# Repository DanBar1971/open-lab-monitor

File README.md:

open-lab-monitor
=================

### Overview

An open hardware microcontroller device for use in research and teaching laboratory settings, and as an independent sensing node.

### PCB

- Nice reference for MAGJACK options:
http://mbed.org/cookbook/Ethernet-RJ45 
- Nice reference for uSD breakout schematic, adafruit:
https://raw.github.com/adafruit/MicroSD-breakout-board/master/usdbreakout.png
 
### Code

Code for controlling the Open Lab Monitor device, the development and goals and applications of which are documented [here](https://github.com/Pioneer-Valley-Open-Science/pioneer-valley-open-science.github.com/issues/8).

The code consists of Arduino code to be loaded on an Arduino-based sensor platform, as well as a Processing and Python interface for interacting with the platform (e.g. plotting sensor values, downloading data as a CSV file). 

#### Notes on the Arduino Code

Some non-standard Arduino libraries are required, frozen versions of which can be found [here](https://github.com/dwblair/open-lab-monitor/tree/master/arduino/libraries).  Copy (or better yet, link) the folders under "libraries" to your "libraries" folder for your Arduino sketchbook:

* ThermistorLib (cversek's library for reading thermistor values) -- latest version found [here](https://github.com/cversek/umass-physics/tree/master/teis/arduino/ThermistorLib).
                                                                  
* SerialCommand (originally Steven Cogswell's slick library for parsing commands over serial)  -- check out his surly [blog post](http://husks.wordpress.com/2011/05/23/a-minimal-arduino-library-for-processing-serial-commands/); we are using the new and improved version hosted on github [here](https://github.com/kroimon/Arduino-SerialCommand)

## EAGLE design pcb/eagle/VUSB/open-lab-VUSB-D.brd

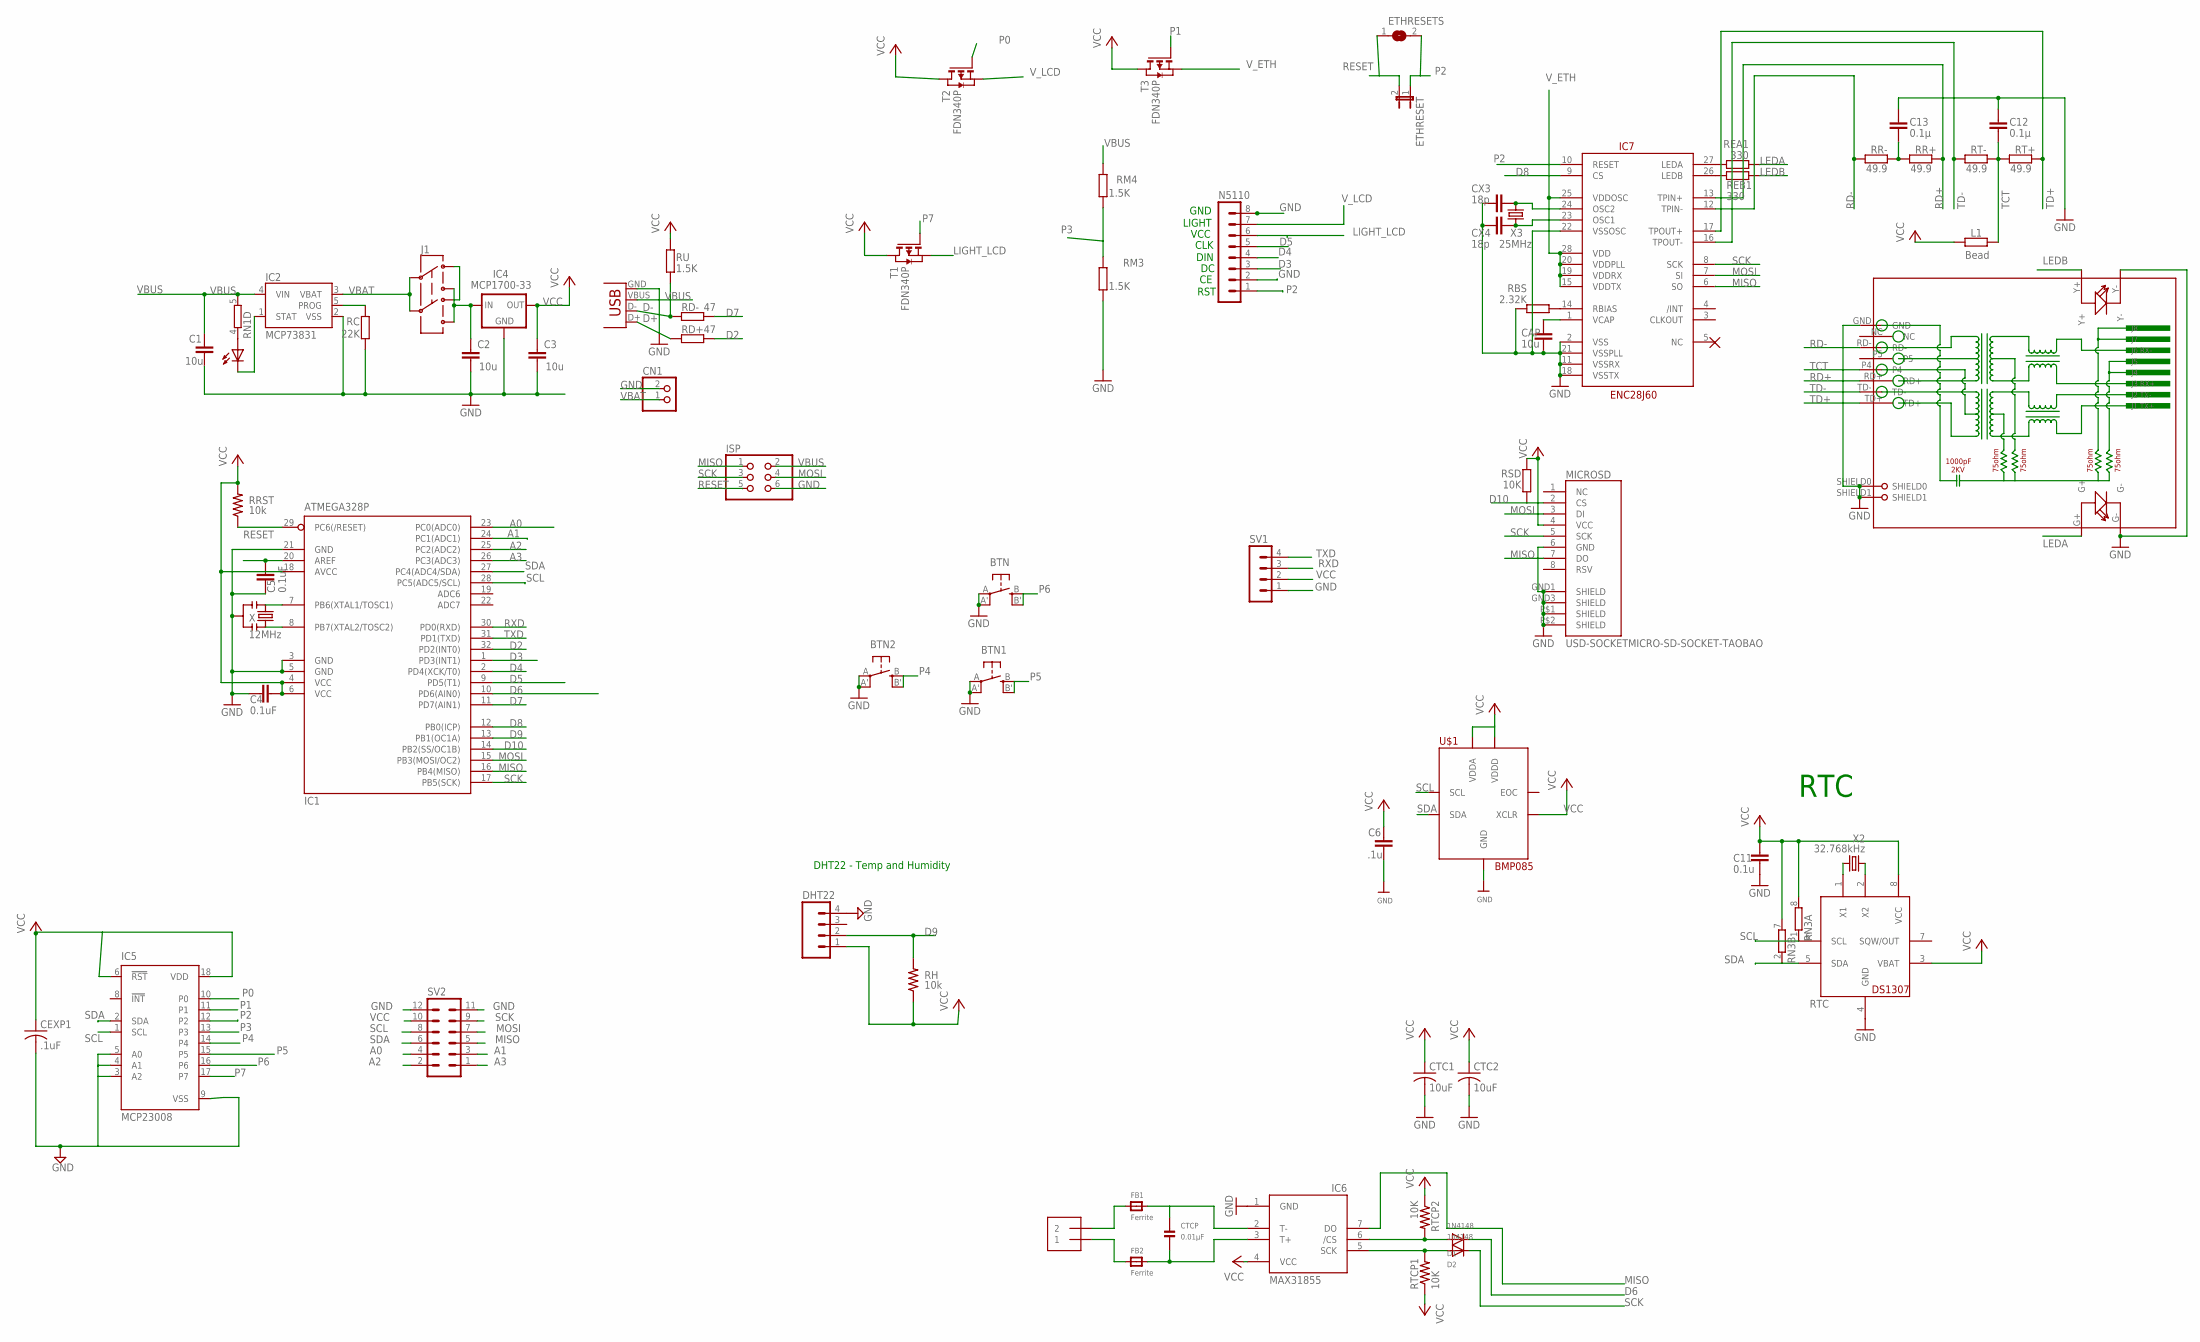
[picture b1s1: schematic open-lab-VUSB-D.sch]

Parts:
BTN, BTN1, BTN2: EVQQ2; EVQ-Q2
C1, C2, C3: 10u; C0805
C4, C5: 0.1uF; C0805
C6: .1u; C0805
C11: 0.1u; C0805
C12, C13: 0.1µ; C0805
CAP: 10u; C0805
CEXP1: .1uF; C0805K
CHG: 0805; CHIPLED_0805
CN1: JST_2PIN-SMT-RA; JST-PH-2-SMT-RA
CTC1, CTC2: 10uF; C0805K
CTCP: 0.01µF; _0805
CX3, CX4: 18p; C0805
D1: 1N4148; SOD-323F
D2: 1n4148; SOD-323F
DHT22: M04LOCK; 1X04_LOCK
ETHRESET: JP1E; JP1
ETHRESETS: SJ
FB1, FB2: Ferrite; _0805
IC1: ATMEGA328P; TQFP32-08
IC2: MCP73831; SOT23-5
IC4: MCP1700-33; SOT23
IC5: MCP23008; SO18W
IC6: MAX31855; SO08
IC7: ENC28J60; SOIC28WLONG
ISP: PINHD-2X3; 2X03
J1: AYZ0202
L1: Bead; R0805
MICROSD: USD-SOCKETMICRO-SD-SOCKET-TAOBAO; MICRO-SD-SOCKET-TAOBAO
N5110: MA08-1
RBS: 2.32K; R0805
RC: 22K; R0805
RD+: 47; R0805
RD-: 47; R0805
REA1: 330; R0805
REB1: 330; R0805
RH: 10k; R0805@1
RJ45: HR911105A
RM3, RM4: 1.5K; R0805
RN1, RN3: 4R-NEXB38V; EXB38V
RR+: 49.9; R0805
RR-: 49.9; R0805
RRST: 10k; R0805@1
RSD: 10K; R0805
RT+: 49.9; R0805
RT-: 49.9; R0805
RTC: DS1307; SO08
RTCP1, RTCP2: 10K; R0805
RU: 1.5K; R0805
SV1: MA04-1
SV2: MA06-2
T1, T2, T3: FDN340P; SOT-23
TCPL: 1X2-3.5MM
U$1: BMP085
X: 12MHz; RESONATOR-SMD
X1: USBSMD; USB-MINIB
X2: 32.768kHz; TC26H
X3: 25MHz; HC49U-V

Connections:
A0: IC1.23 (PC0(ADC0)), SV2.4
A1: IC1.24 (PC1(ADC1)), SV2.3
A2: IC1.25 (PC2(ADC2)), SV2.2
A3: IC1.26 (PC3(ADC3)), SV2.1
AREF: C5.2, IC1.20 (AREF)
CS: D1.A, IC6.6 (/CS), RTCP2.2
D2: IC1.32 (PD2(INT0)), RD+.2
D3: IC1.1 (PD3(INT1)), N5110.3
D4: IC1.2 (PD4(XCK/T0)), N5110.4
D5: IC1.9 (PD5(T1)), N5110.5
D6: D1.C, IC1.10 (PD6(AIN0))
D7: IC1.11 (PD7(AIN1)), RD-.2
D8: IC1.12 (PB0(ICP)), IC7.9 (CS)
D9: DHT22.2, IC1.13 (PB1(OC1A)), RH.2
D10: IC1.14 (PB2(SS/OC1B)), MICROSD.2 (CS), RSD.1
D+: RD+.1, X1.D+
D-: RD-.1, RU.1, X1.D-
GND: BTN.A, BTN.A' (P1), BTN1.A, BTN1.A' (P1), BTN2.A, BTN2.A' (P1), C1.2, C2.2, C3.2, C4.1, C5.1, C6.2, C11.2, C12.1, C13.1, CAP.2, CEXP1.2, CN1.2 (1), CTC1.2, CTC2.2, CX3.2, CX4.2, DHT22.4, IC1.3 (GND), IC1.5 (GND), IC1.21 (GND), IC2.2 (VSS), IC4.1 (GND), IC5.3 (A2), IC5.4 (A1), IC5.5 (A0), IC5.9 (VSS), IC6.1 (GND), IC7.2 (VSS), IC7.11 (VSSRX), IC7.18 (VSSTX), IC7.21 (VSSPLL), IC7.22 (VSSOSC), ISP.6, MICROSD.6 (GND), MICROSD.GND1 (SHIELD), MICROSD.GND3 (SHIELD), MICROSD.P$1 (SHIELD), MICROSD.P$2 (SHIELD), N5110.2, N5110.8, RBS.1, RC.1, RJ45.G-, RJ45.GND, RJ45.SHIELD0, RJ45.SHIELD1, RJ45.Y-, RM3.1, RTC.4 (GND), SV1.1, SV2.11, SV2.12, U$1.P$1 (GND), X.2, X1.GND
LEDA: REA1.2, RJ45.G+
LEDB: REB1.2, RJ45.Y+
LIGHT_LCD: N5110.6, T1.2 (S)
MISO: IC1.16 (PB4(MISO)), IC6.7 (DO), IC7.6 (SO), ISP.1, MICROSD.7 (DO), SV2.5
MOSI: IC1.15 (PB3(MOSI/OC2)), IC7.7 (SI), ISP.4, MICROSD.3 (DI), SV2.7
unnamed: J1.3 (1), J1.6 (4)
unnamed: IC1.7 (PB6(XTAL1/TOSC1)), X.1
unnamed: IC1.8 (PB7(XTAL2/TOSC2)), X.3
unnamed: CHG.C, IC2.1 (STAT)
unnamed: IC2.5 (PROG), RC.2
unnamed: FB1.1, TCPL.2
unnamed: CTCP.1, FB1.2, IC6.2 (T-)
unnamed: CHG.A, RN1.4 (1)
unnamed: FB2.1, TCPL.1
unnamed: CTCP.2, FB2.2, IC6.3 (T+)
unnamed: RTC.1 (X1), X2.2
unnamed: RTC.2 (X2), X2.1
unnamed: IC7.27 (LEDA), REA1.1
unnamed: IC7.26 (LEDB), REB1.1
unnamed: CAP.1, IC7.1 (VCAP)
unnamed: CX3.1, IC7.24 (OSC2), X3.2
unnamed: CX4.1, IC7.23 (OSC1), X3.1
unnamed: C13.2, RR+.2, RR-.1
unnamed: IC7.14 (RBIAS), RBS.2
P0: IC5.10 (P0), T2.3 (G)
P1: IC5.11 (P1), T3.3 (G)
P2: ETHRESET.1, ETHRESETS.2, IC5.12 (P2), IC7.10 (RESET), N5110.1
P3: IC5.13 (P3), RM3.2, RM4.1
P4: BTN2.B (S), BTN2.B' (S1), IC5.14 (P4)
P5: BTN1.B (S), BTN1.B' (S1), IC5.15 (P5)
P6: BTN.B (S), BTN.B' (S1), IC5.16 (P6)
P7: IC5.17 (P7), T1.3 (G)
RD+: IC7.13 (TPIN+), RJ45.RD+, RR+.1
RD-: IC7.12 (TPIN-), RJ45.RD-, RR-.2
RESET: ETHRESET.2, ETHRESETS.1, IC1.29 (PC6(/RESET)), ISP.5, RRST.1
RXD: IC1.30 (PD0(RXD)), SV1.3
SCK: D2.C, IC1.17 (PB5(SCK)), IC7.8 (SCK), ISP.3, MICROSD.5 (SCK), SV2.9
SCK1: D2.A, IC6.5 (SCK), RTCP1.2
SCL: IC1.28 (PC5(ADC5/SCL)), IC5.1 (SCL), RN3.1, RTC.6 (SCL), SV2.8, U$1.P$6 (SCL)
SDA: IC1.27 (PC4(ADC4/SDA)), IC5.2 (SDA), RN3.2 (1), RTC.5 (SDA), SV2.6, U$1.P$7 (SDA)
TCT: C12.2, L1.1, RJ45.P4, RT+.2, RT-.1
TD+: IC7.17 (TPOUT+), RJ45.TD+, RT+.1
TD-: IC7.16 (TPOUT-), RJ45.TD-, RT-.2
TXD: IC1.31 (PD1(TXD)), SV1.4
VBAT: CN1.1 (2), IC2.3 (VBAT), J1.2, J1.5
VBUS: C1.1, IC2.4 (VIN), ISP.2, RM4.2, RN1.5 (2), X1.VBUS
VCC: C3.1, C4.2, C6.1, C11.1, CEXP1.1, CTC1.1, CTC2.1, DHT22.1, IC1.4 (VCC), IC1.6 (VCC), IC1.18 (AVCC), IC4.2 (OUT), IC5.6 (!RST), IC5.18 (VDD), IC6.4 (VCC), L1.2, MICROSD.4 (VCC), RH.1, RN3.7 (2), RN3.8 (2), RRST.2, RSD.2, RTC.3 (VBAT), RTC.8 (VCC), RTCP1.1, RTCP2.1, RU.2, SV1.2, SV2.10, T1.1 (D), T2.1 (D), T3.1 (D), U$1.P$3 (VDDA), U$1.P$4 (VDDD), U$1.P$8 (XCLR)
VDD: C2.1, IC4.3 (IN), J1.1 (3), J1.4 (6)
V_ETH: IC7.15 (VDDTX), IC7.19 (VDDRX), IC7.20 (VDDPLL), IC7.25 (VDDOSC), IC7.28 (VDD), T3.2 (S)
V_LCD: N5110.7, T2.2 (S)

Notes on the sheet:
RST
DIN
CLK
VCC
LIGHT
GND
RTC
DHT22 - Temp and Humidity

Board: 2 copper layers, 72 parts (4 on the bottom side), 68 nets, no tracks yet.

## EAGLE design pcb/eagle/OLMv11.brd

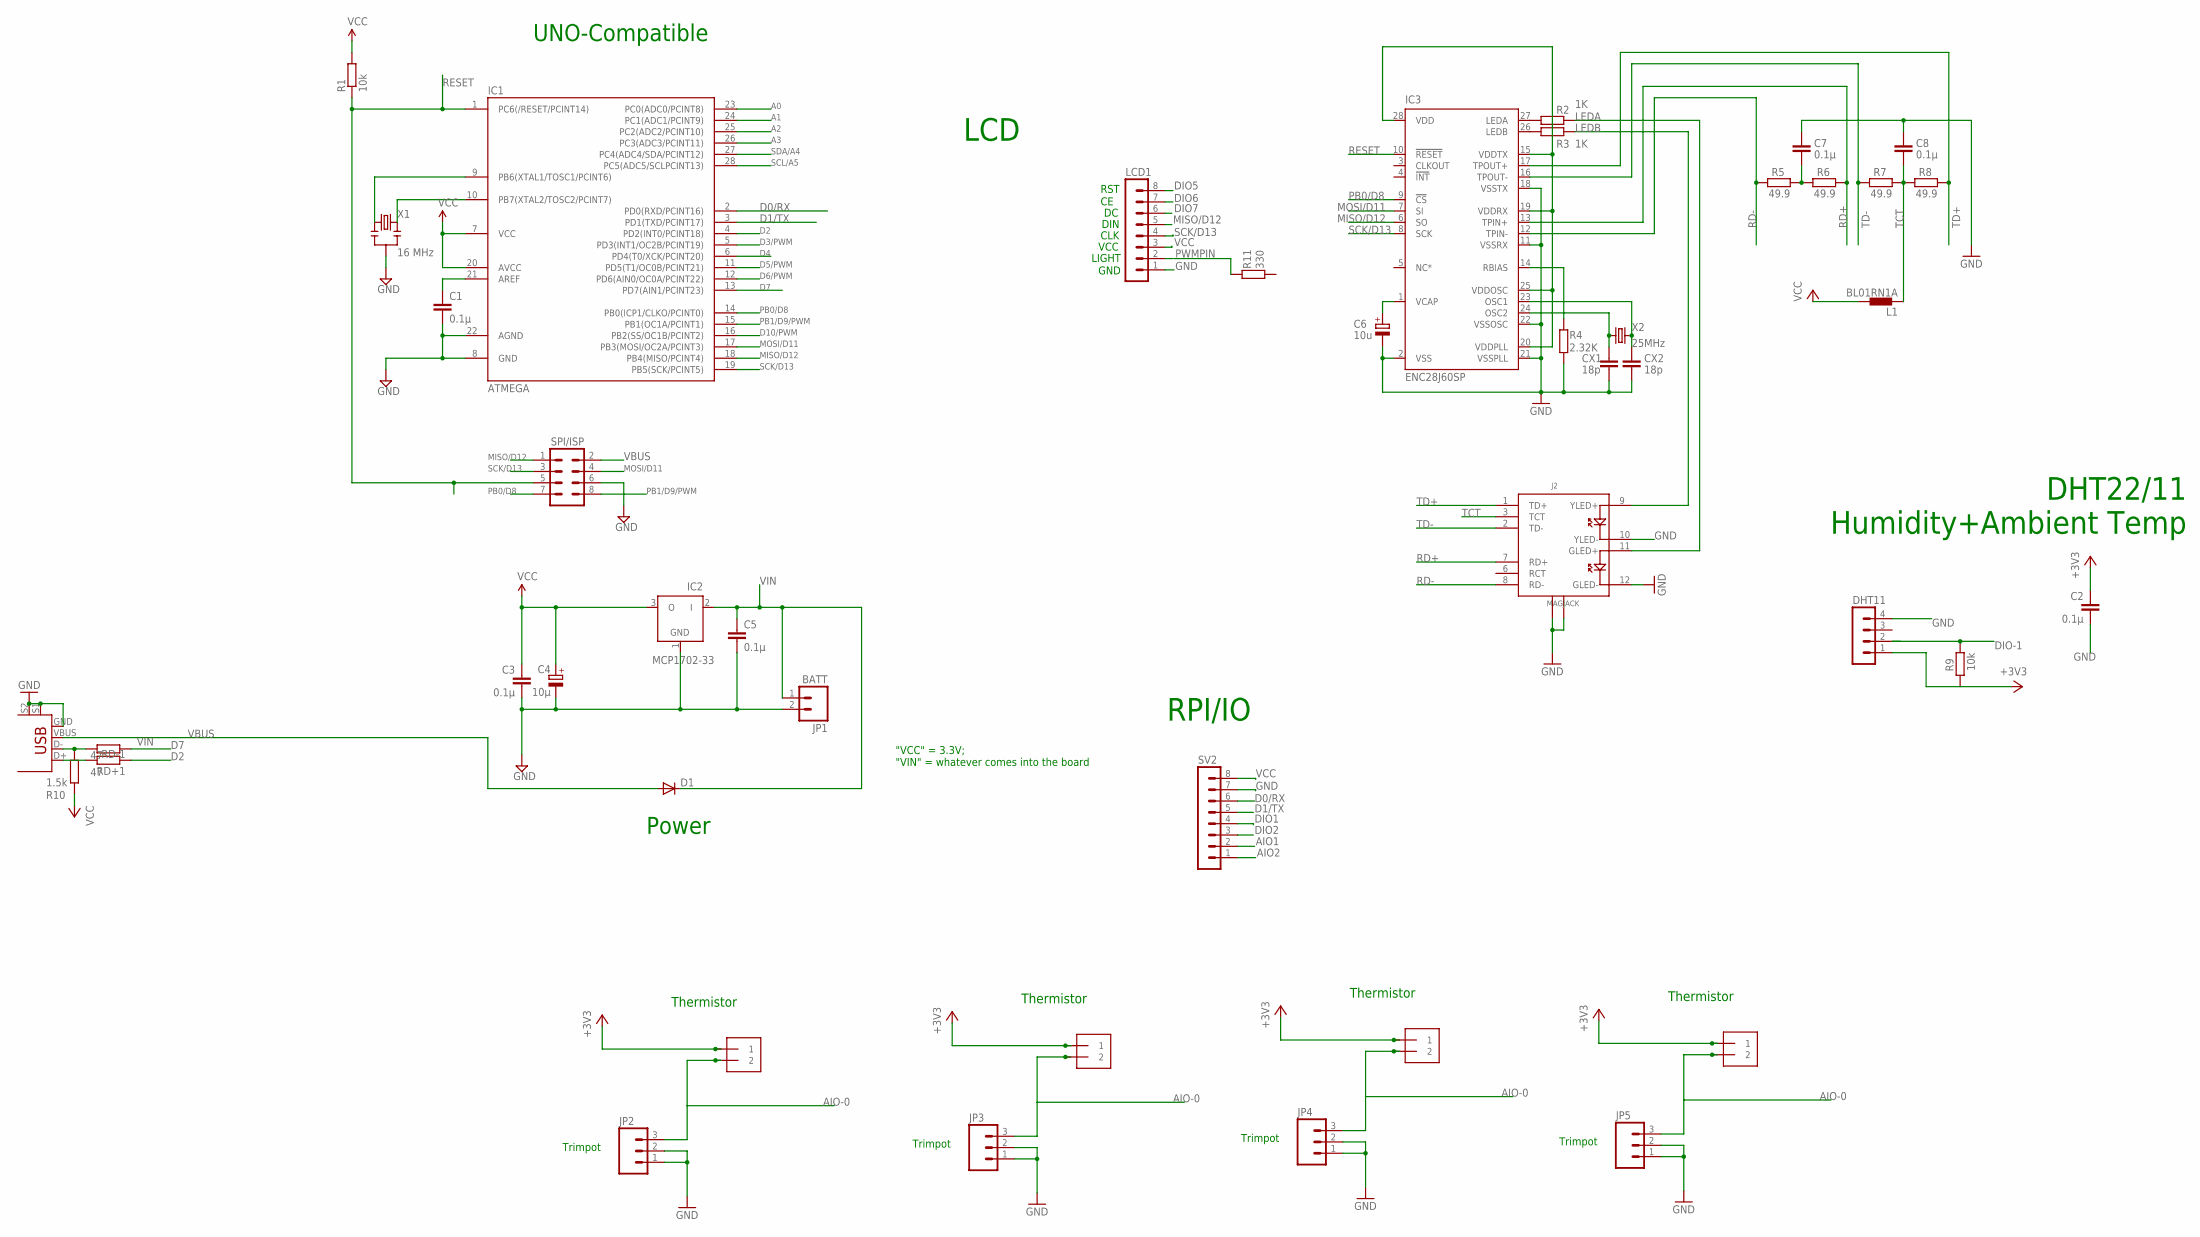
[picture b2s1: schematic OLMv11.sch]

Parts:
C1, C2, C3, C5, C7, C8: 0.1µ; C025-024X044
C4: 10µ; E1,8-4
C6: 10u; E1,8-4
CX1, CX2: 18p; C025-024X044
D1: DIODE-D-5; D-5
DHT11: MA04-1
IC1: ATMEGA; DIL28-3
IC2: MCP1702-33; TO92
IC3: ENC28J60SP; DIL28-3
J1, J3, J4, J5: 1X2-3.5MM
J2: MAGJACK
JP1: BATT; 1X02_LOCK_LONGPADS
JP2, JP3, JP4, JP5: M03PTH; 1X03
L1: BL01RN1A
LCD1: MA08-1
R1, R9: 10k; 0204/7
R2, R3: 1K; 0204/7
R4: 2.32K; 0204/7
R5, R6, R7, R8: 49.9; 0204/7
R10: 1.5k; 0204/7
R11: 330; 0204/7
RD+1: 47; 0204/7
RD-1: 47; 0204/7
SV1: SPI/ISP; MA04-2
SV2: MA08-1
USB: USB+SHIELD; USB-B-PTH
X1: 16 MHz; RESONATOR-PTH
X2: 25MHz; HC49US

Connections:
+3V3: C2.1, DHT11.1, J1.1, J3.1, J4.1, J5.1, R9.1
A0: IC1.23 (PC0(ADC0/PCINT8))
A1: IC1.24 (PC1(ADC1/PCINT9))
A2: IC1.25 (PC2(ADC2/PCINT10))
A3: IC1.26 (PC3(ADC3/PCINT11))
AIO1: SV2.2
AIO2: SV2.1
AIO-0: J1.2, J3.2, J4.2, J5.2, JP2.3, JP3.3, JP4.3, JP5.3
D0/RX: IC1.2 (PD0(RXD/PCINT16)), SV2.6
D1/TX: IC1.3 (PD1(TXD/PCINT17)), SV2.5
D2: IC1.4 (PD2(INT0/PCINT18)), RD+1.1
D3/PWM: IC1.5 (PD3(INT1/OC2B/PCINT19))
D4: IC1.6 (PD4(T0/XCK/PCINT20))
D5/PWM: IC1.11 (PD5(T1/OC0B/PCINT21))
D6/PWM: IC1.12 (PD6(AIN0/OC0A/PCINT22))
D7: IC1.13 (PD7(AIN1/PCINT23)), RD-1.1
D10/PWM: IC1.16 (PB2(SS/OC1B/PCINT2))
DIO1: SV2.4
DIO2: SV2.3
DIO5: LCD1.8
DIO6: LCD1.7
DIO7: LCD1.6
DIO-1: DHT11.2, R9.2
GND: C1.2, C2.2, C3.2, C4.-, C5.2, C6.-, C7.1, C8.1, CX1.2, CX2.2, DHT11.4, IC1.8 (GND), IC1.22 (AGND), IC2.1 (GND), IC3.2 (VSS), IC3.11 (VSSRX), IC3.18 (VSSTX), IC3.21 (VSSPLL), IC3.22 (VSSOSC), J2.10 (YLED-), J2.12 (GLED-), J2.M1 (GND1), J2.M2 (GND2), JP1.2, JP2.1, JP2.2, JP3.1, JP3.2, JP4.1, JP4.2, JP5.1, JP5.2, LCD1.1, R4.2, SV1.6, SV2.7, USB.GND, USB.S1, USB.S2, X1.2
LEDA: J2.11 (GLED+), R2.2
LEDB: J2.9 (YLED+), R3.2
MISO/D12: IC1.18 (PB4(MISO/PCINT4)), IC3.6 (SO), LCD1.5, SV1.1
MOSI/D11: IC1.17 (PB3(MOSI/OC2A/PCINT3)), IC3.7 (SI), SV1.4
unnamed: IC1.9 (PB6(XTAL1/TOSC1/PCINT6)), X1.1
unnamed: C1.1, IC1.21 (AREF)
unnamed: IC1.10 (PB7(XTAL2/TOSC2/PCINT7)), X1.3
unnamed: IC3.27 (LEDA), R2.1
unnamed: RD+1.2, USB.D+
unnamed: IC3.26 (LEDB), R3.1
unnamed: R10.1, RD-1.2, USB.D-
unnamed: C6.+, IC3.1 (VCAP)
unnamed: IC3.14 (RBIAS), R4.1
unnamed: CX1.1, IC3.24 (OSC2), X2.1
unnamed: CX2.1, IC3.23 (OSC1), X2.2
unnamed: C7.2, R5.2, R6.1
PB0/D8: IC1.14 (PB0(ICP1/CLKO/PCINT0)), IC3.9 (!CS), SV1.7
PB1/D9/PWM: IC1.15 (PB1(OC1A/PCINT1)), SV1.8
PWMPIN: LCD1.2
RD+: IC3.13 (TPIN+), J2.7 (RD+), R6.2
RD-: IC3.12 (TPIN-), J2.8 (RD-), R5.1
RESET: IC1.1 (PC6(/RESET/PCINT14)), IC3.10 (!RESET), R1.1, SV1.5
SCK/D13: IC1.19 (PB5(SCK/PCINT5)), IC3.8 (SCK), LCD1.4, SV1.3
SCL/A5: IC1.28 (PC5(ADC5/SCLPCINT13))
SDA/A4: IC1.27 (PC4(ADC4/SDA/PCINT12))
TCT: C8.2, J2.3 (TCT), L1.1, R7.2, R8.1
TD+: IC3.17 (TPOUT+), J2.1 (TD+), R8.2
TD-: IC3.16 (TPOUT-), J2.2 (TD-), R7.1
VBUS: D1.A, SV1.2
VCC: C3.1, C4.+, IC1.7 (VCC), IC1.20 (AVCC), IC2.3 (O), IC3.15 (VDDTX), IC3.19 (VDDRX), IC3.20 (VDDPLL), IC3.25 (VDDOSC), IC3.28 (VDD), L1.2, LCD1.3, R1.2, R10.2, SV2.8
VIN: C5.1, D1.C, IC2.2 (I), JP1.1, USB.VBUS

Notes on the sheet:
UNO-Compatible
Power
"VCC" = 3.3V; "VIN" = whatever comes into the board
Thermistor
DHT22/11 Humidity+Ambient Temp
Trimpot
LCD
RPI/IO
RST
DIN
CLK
VCC
LIGHT
GND

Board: 2 copper layers, 45 parts (0 on the bottom side), 36 nets, no tracks yet.

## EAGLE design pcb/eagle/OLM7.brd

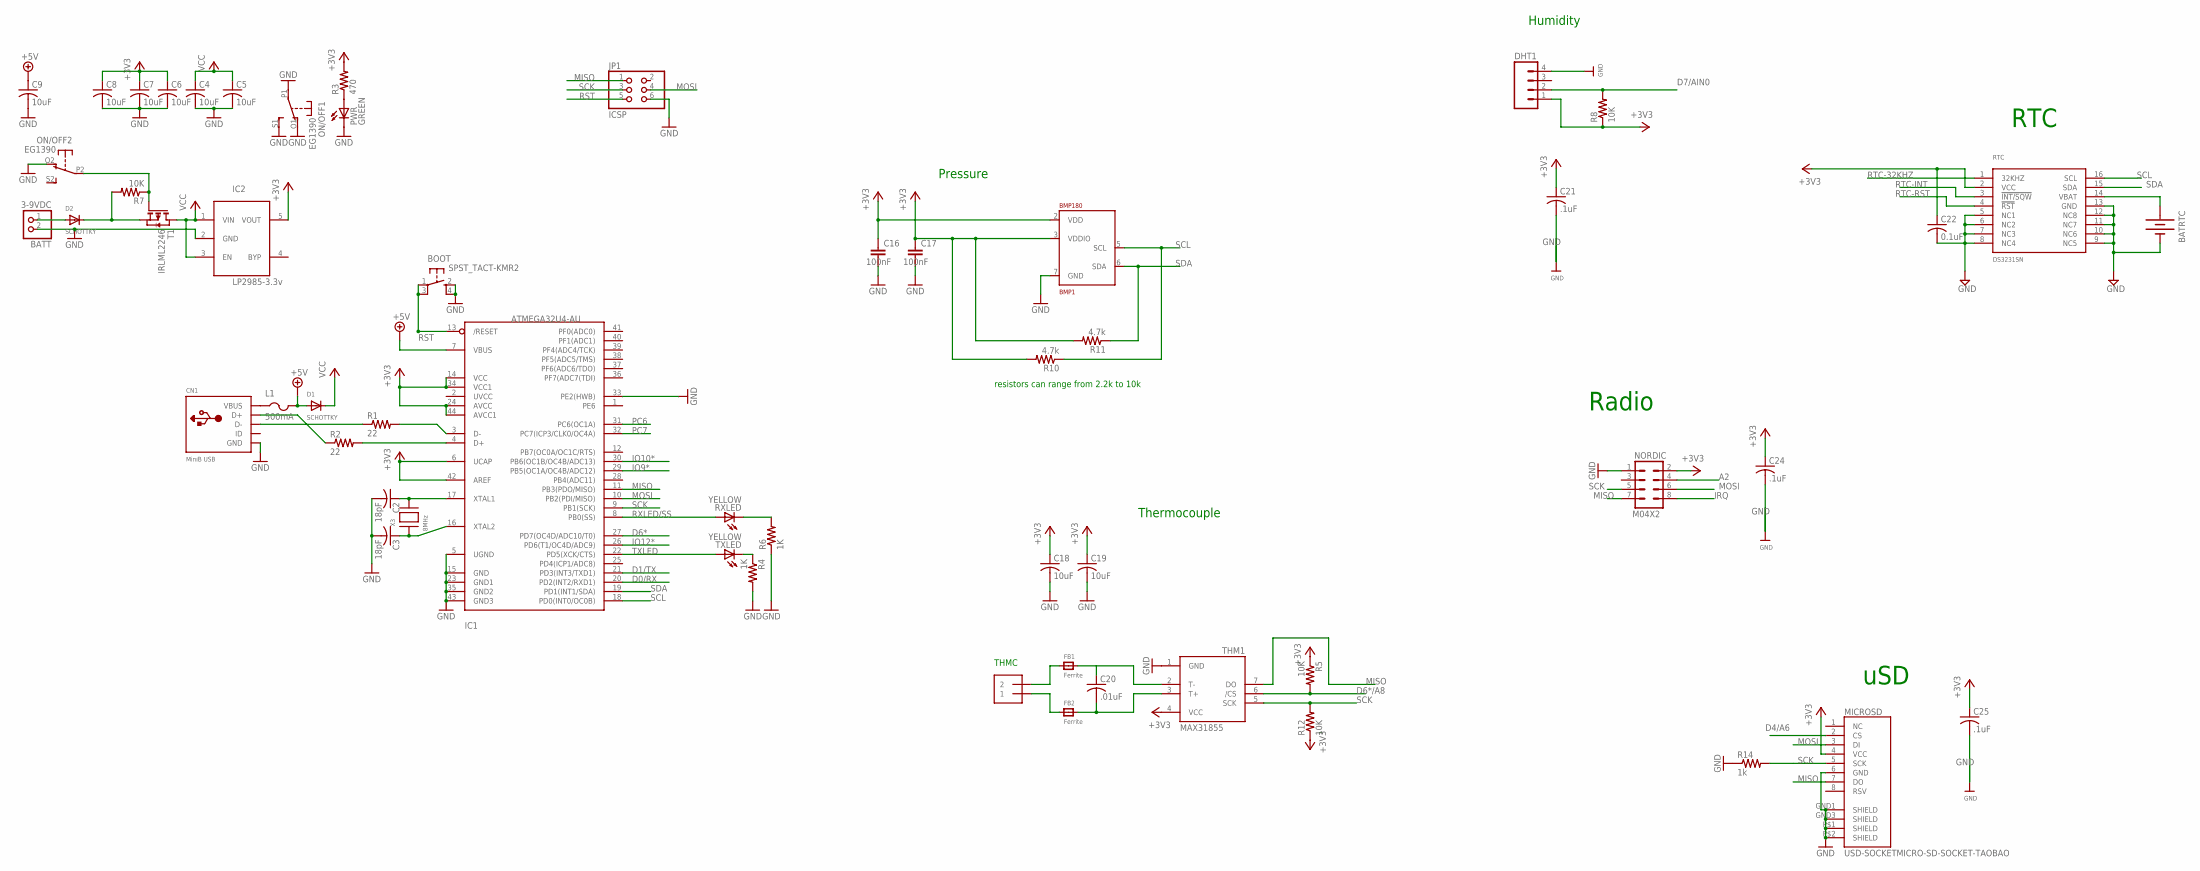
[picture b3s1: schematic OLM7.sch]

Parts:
BATRTC: BATTERYBATTERY_12MM_SMT; BATTCON_12MM_SMT
BATT: 3-9VDC; JST-PH-2-SMT-RA
BMP1: BMP180; LGA7
BOOT: SPST_TACT-KMR2; KMR2
C2, C3: 18pF; C0805K
C4, C5, C6, C7, C8, C9: 10uF; C0805K
C16, C17: 100nF; C0805
C18, C19: 10uF; C0805
C20: .01uF; C0805
C21, C24, C25: .1uF; C0805
C22: 0.1uF; C0805
CN1: MiniB USB; USB-MINIB_LARGER
D1, D2: SCHOTTKY; SOD-123
DHT1: M04LOCK; 1X04_LOCK
FB1, FB2: Ferrite; _0805
IC1: ATMEGA32U4-AU; TQFP44
IC2: LP2985-3.3v; SOT23-5L
JP1: ICSP; 2X03
L1: 500mA; R1206
MICROSD: USD-SOCKETMICRO-SD-SOCKET-TAOBAO; MICRO-SD-SOCKET-TAOBAO
NORDIC: M04X2; 2X4
ON/OFF: EG1390
PWR: GREEN; CHIPLED_0805
R1, R2: 22; R0805
R3: 470; R0805
R4, R6: 1K; R0805
R5, R7, R8, R12: 10K; R0805
R10, R11: 4.7k; R0805
R14: 1k; R0805
RTC: DS3231SN; SO16W
RXLED: YELLOW; CHIPLED_0805
T1: IRLML2246; SOT-23
THM1: MAX31855; SO08
THMC: 1X2-3.5MM
TXLED: YELLOW; CHIPLED_0805
X3: 8MHz; NX5032

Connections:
+3V3: BMP1.2 (VDD), BMP1.3 (VDDIO), C6.1, C7.1, C8.1, C16.1, C17.1, C18.1, C19.1, C21.1, C22.1, C24.1, C25.1, DHT1.1, IC1.6 (UCAP), IC1.14 (VCC), IC1.24 (AVCC), IC1.34 (VCC1), IC1.42 (AREF), IC1.44 (AVCC1), IC2.5 (VOUT), MICROSD.4 (VCC), NORDIC.2, R3.2, R5.1, R8.1, R10.2, R11.2, R12.1, RTC.2 (VCC), THM1.4 (VCC)
+5V: C9.1, D1.A, IC1.7 (VBUS), L1.2
A2: NORDIC.4
D0/RX: IC1.20 (PD2(INT2/RXD1))
D1/TX: IC1.21 (PD3(INT3/TXD1))
D4/A6: MICROSD.2 (CS)
D6*: IC1.27 (PD7(OC4D/ADC10/T0))
D6*/A8: R5.2, THM1.6 (/CS)
D7/AIN0: DHT1.2, R8.2
GND: BATRTC.P$1 (-), BATT.2 (1), BMP1.7 (GND), BOOT.2 (S), BOOT.4 (S1), C2.2, C3.2, C4.2, C5.2, C6.2, C7.2, C8.2, C9.2, C16.2, C17.2, C18.2, C19.2, C21.2, C22.2, C24.2, C25.2, CN1.GND, DHT1.4, IC1.5 (UGND), IC1.15 (GND), IC1.23 (GND1), IC1.33 (PE2(HWB)), IC1.35 (GND2), IC1.43 (GND3), IC2.2 (GND), JP1.6, MICROSD.6 (GND), MICROSD.GND1 (SHIELD), MICROSD.GND3 (SHIELD), MICROSD.P$1 (SHIELD), MICROSD.P$2 (SHIELD), NORDIC.1, ON/OFF.O1 (O), ON/OFF.O2 (O), ON/OFF.P1, ON/OFF.S1 (S), PWR.C, R4.2, R6.1, R14.1, RTC.5 (NC1), RTC.6 (NC2), RTC.7 (NC3), RTC.8 (NC4), RTC.9 (NC5), RTC.10 (NC6), RTC.11 (NC7), RTC.12 (NC8), RTC.13 (GND), THM1.1 (GND)
IO9*: IC1.29 (PB5(OC1A/OC4B/ADC12))
IO10*: IC1.30 (PB6(OC1B/OC4B/ADC13))
IO12*: IC1.26 (PD6(T1/OC4D/ADC9))
IRQ: NORDIC.8
MISO: IC1.11 (PB3(PDO/MISO)), JP1.1, MICROSD.7 (DO), NORDIC.7, THM1.7 (DO)
MOSI: IC1.10 (PB2(PDI/MISO)), JP1.4, MICROSD.3 (DI), NORDIC.6
unnamed: PWR.A, R3.1
unnamed: CN1.D+, R2.1
unnamed: IC1.3 (D-), R1.2
unnamed: IC1.4 (D+), R2.2
unnamed: CN1.D-, R1.1
unnamed: D2.C, R7.2, T1.2 (S)
unnamed: BATT.1 (2), D2.A
unnamed: C2.1, IC1.17 (XTAL1), X3.P$2
unnamed: C3.1, IC1.16 (XTAL2), X3.P$1
unnamed: R4.1, TXLED.C
unnamed: R6.2, RXLED.C
unnamed: ON/OFF.P2, R7.1, T1.3 (G)
unnamed: BATRTC.P$2 (+), RTC.14 (VBAT)
unnamed: FB1.1, THMC.2
unnamed: C20.1, FB1.2, THM1.2 (T-)
unnamed: FB2.1, THMC.1
unnamed: C20.2, FB2.2, THM1.3 (T+)
PC6: IC1.31 (PC6(OC1A))
PC7: IC1.32 (PC7(ICP3/CLK0/OC4A))
RST: BOOT.1, BOOT.3 (P1), IC1.13 (/RESET), JP1.5
RTC-32KHZ: RTC.1 (32KHZ)
RTC-INT: RTC.3 (!INT/SQW)
RTC-RST: RTC.4 (!RST)
RXLED/SS: IC1.8 (PB0(SS)), RXLED.A
SCK: IC1.9 (PB1(SCK)), JP1.3, MICROSD.5 (SCK), NORDIC.5, R12.2, THM1.5 (SCK)
SCK1: R14.2
SCL: BMP1.5 (SCL), IC1.18 (PD0(INT0/OC0B)), R10.1, RTC.16 (SCL)
SDA: BMP1.6 (SDA), IC1.19 (PD1(INT1/SDA)), R11.1, RTC.15 (SDA)
TXLED: IC1.22 (PD5(XCK/CTS)), TXLED.A
VBUS: CN1.VBUS, L1.1
VCC: C4.1, C5.1, D1.C, IC2.1 (VIN), IC2.3 (EN), T1.1 (D)

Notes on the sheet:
Pressure
resistors can range from 2.2k to 10k
Thermocouple
THMC
Humidity
Radio
RTC
uSD

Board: 2 copper layers, 54 parts (0 on the bottom side), 32 nets, no tracks yet.

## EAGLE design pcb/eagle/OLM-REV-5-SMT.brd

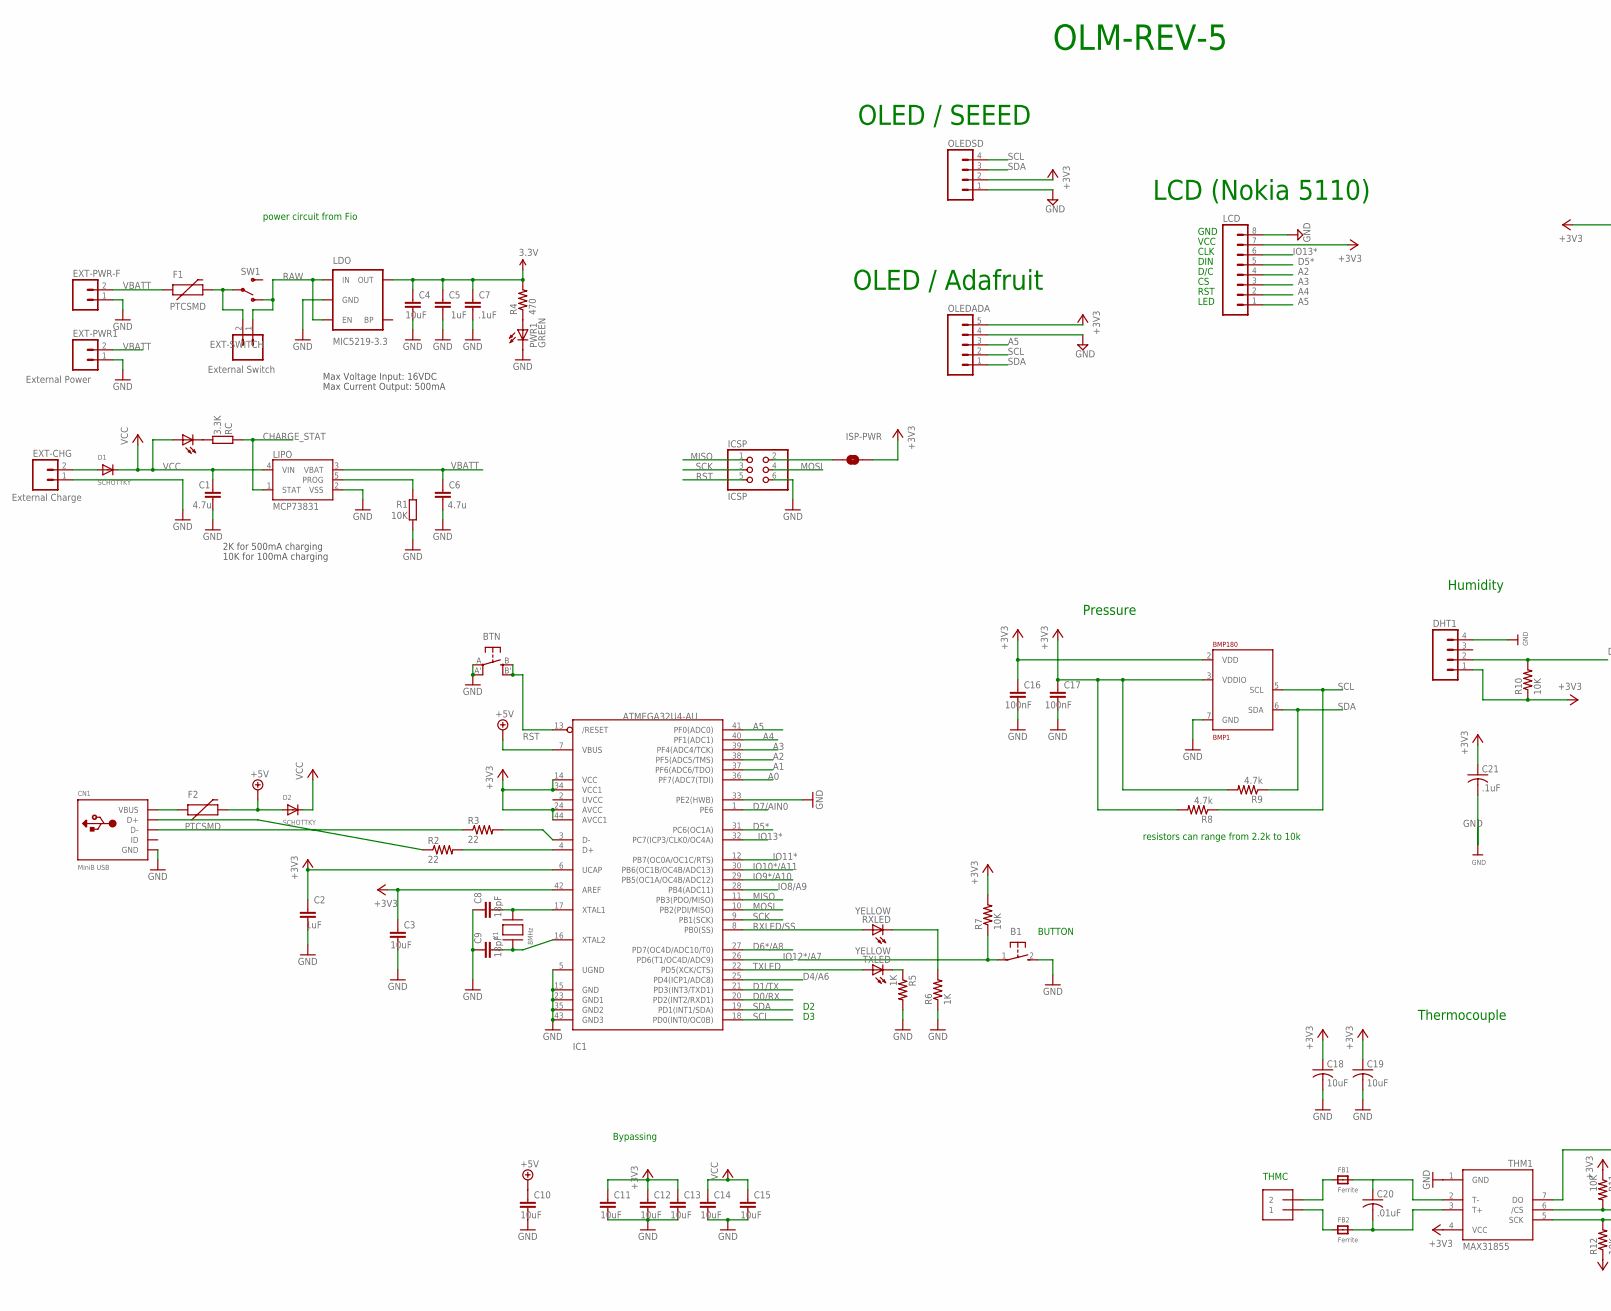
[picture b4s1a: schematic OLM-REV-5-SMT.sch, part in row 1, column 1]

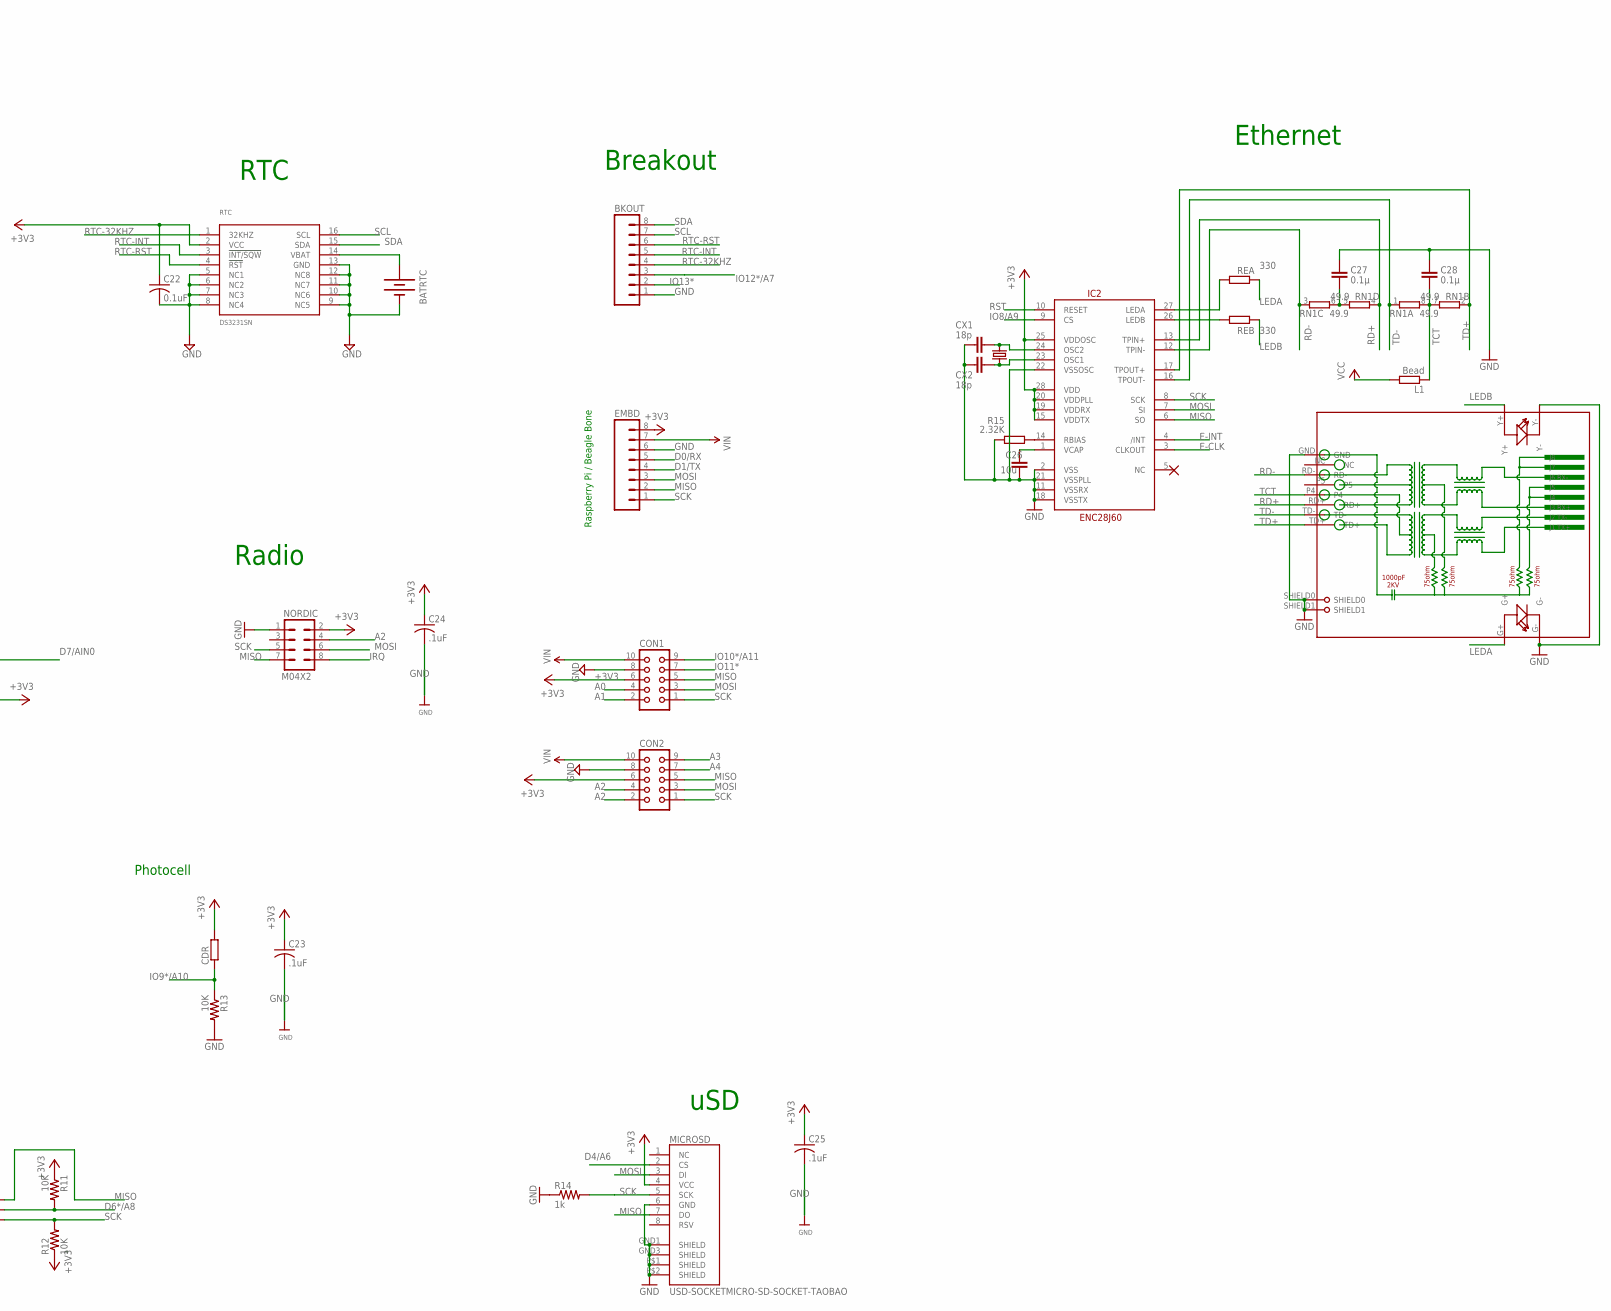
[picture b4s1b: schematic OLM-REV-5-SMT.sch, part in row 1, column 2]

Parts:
B1: 31-XX; B3F-31XX
BATRTC: BATTERYBATTERY_12MM_SMT; BATTCON_12MM_SMT
BKOUT: M08LOCK; 1X08_LOCK
BMP1: BMP180; LGA7
BTN: EVQQ2; EVQ-Q2
C1, C6: 4.7u; C0805
C2, C5: 1uF; C0805
C3, C4, C10, C11, C12, C13, C14, C15, C18, C19: 10uF; C0805
C7, C21, C23, C24, C25: .1uF; C0805
C8, C9: 18pF; C0805
C16, C17: 100nF; C0805
C20: .01uF; C0805
C22: 0.1uF; C0805
C26: 10u; C0805
C27, C28: 0.1µ; C0805
CDR: R-EU_0204/7; 0204/7
CHG1: 0805; CHIPLED_0805
CN1: MiniB USB; USB-MINIB_LARGER
CON1, CON2: CON10L
CX1, CX2: 18p; C0805
D1, D2: SCHOTTKY; SOD-123
DHT1: M04LOCK; 1X04_LOCK
EMBD: M08LOCK; 1X08_LOCK
EXT-CHG: External Charge; 1X02
EXT-PWR1: External Power; 1X02
EXT-PWR-F: M02-JST-2MM-SMT; JST-2-SMD
EXT-SWITCH: External Switch; 1X02
EXTL: 25MHz; CRYSTAL-SMD-10.5X4.8-2PIN
F1, F2: PTCSMD; PTC-1206
FB1, FB2: Ferrite; _0805
IC1: ATMEGA32U4-AU; TQFP44
IC2: ENC28J60; SOIC28WLONG
ICSP: ICSP; 2X03
ISP-PWR: SOLDERJUMPERTRACE; SJ_2S-TRACE
L1: Bead; R0805
LCD: M08LOCK; 1X08_LOCK
LDO: MIC5219-3.3; SOT23-5
LIPO: MCP73831; SOT23-5
MICROSD: USD-SOCKETMICRO-SD-SOCKET-TAOBAO; MICRO-SD-SOCKET-TAOBAO
NORDIC: M04X2; 2X4
OLEDADA: M05LOCK; 1X05_LOCK
OLEDSD: M04LOCK; 1X04_LOCK
PWR1: GREEN; CHIPLED_0805
R1, R7, R10, R11, R12, R13: 10K; R0805
R2, R3: 22; R0805
R4: 470; R0805
R5, R6: 1K; R0805
R8, R9: 4.7k; R0805
R14: 1k; R0805
R15: 2.32K; R0805
RC: 3.3K; R0805
REA: 330; R0805
REB: 330; R0805
RJ1: HR911105A
RN1: 49.9; EXB38V
RTC: DS3231SN; SO16W
RXLED: YELLOW; CHIPLED_0805
SW1: SPDT; SWITCH-SPDT-SMD
THM1: MAX31855; SO08
THMC: 1X2-3.5MM
TXLED: YELLOW; CHIPLED_0805
X1: 8MHz; NX5032

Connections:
3.3V: C4.1, C5.1, C7.1, LDO.5 (OUT), R4.2
+3V3: BMP1.2 (VDD), BMP1.3 (VDDIO), C2.1, C3.1, C11.1, C12.1, C13.1, C16.1, C17.1, C18.1, C19.1, C21.1, C22.1, C23.1, C24.1, C25.1, CDR.2, CON1.6, CON2.6, DHT1.1, EMBD.8, IC1.6 (UCAP), IC1.14 (VCC), IC1.24 (AVCC), IC1.34 (VCC1), IC1.42 (AREF), IC1.44 (AVCC1), IC2.15 (VDDTX), IC2.19 (VDDRX), IC2.20 (VDDPLL), IC2.25 (VDDOSC), IC2.28 (VDD), ISP-PWR.2, LCD.7, MICROSD.4 (VCC), NORDIC.2, OLEDADA.5, OLEDSD.2, R7.2, R8.2, R9.2, R10.1, R11.1, R12.1, RTC.2 (VCC), THM1.4 (VCC)
+5V: C10.1, D2.A, F2.2, IC1.7 (VBUS)
A0: CON1.4
A1: CON1.2
A2: CON2.2, CON2.4, LCD.4, NORDIC.4
A3: CON2.9, LCD.3
A4: CON2.7, LCD.2
A5: LCD.1, OLEDADA.3
CHARGE_STAT: LIPO.1 (STAT), RC.2
D0/RX: EMBD.5
D1/TX: EMBD.4
D4/A6: MICROSD.2 (CS)
D5*: LCD.5
D6*/A8: R11.2, THM1.6 (/CS)
D7/AIN0: DHT1.2, R10.2
E-CLK: IC2.3 (CLKOUT)
E-INT: IC2.4 (/INT)
GND: B1.2 (S), BATRTC.P$1 (-), BKOUT.1, BMP1.7 (GND), BTN.A, BTN.A' (P1), C1.2, C2.2, C3.2, C4.2, C5.2, C6.2, C7.2, C8.1, C9.1, C10.2, C11.2, C12.2, C13.2, C14.2, C15.2, C16.2, C17.2, C18.2, C19.2, C21.2, C22.2, C23.2, C24.2, C25.2, C26.2, C27.1, C28.1, CN1.GND, CON1.8, CON2.8, CX1.2, CX2.2, DHT1.4, EMBD.6, EXT-CHG.1, EXT-PWR1.1, EXT-PWR-F.1, IC1.5 (UGND), IC1.15 (GND), IC1.23 (GND1), IC1.35 (GND2), IC1.43 (GND3), IC2.2 (VSS), IC2.11 (VSSRX), IC2.18 (VSSTX), IC2.21 (VSSPLL), IC2.22 (VSSOSC), ICSP.6, LCD.8, LDO.2 (GND), LIPO.2 (VSS), MICROSD.6 (GND), MICROSD.GND1 (SHIELD), MICROSD.GND3 (SHIELD), MICROSD.P$1 (SHIELD), MICROSD.P$2 (SHIELD), NORDIC.1, OLEDADA.4, OLEDSD.1, PWR1.C, R1.1, R5.2, R6.1, R13.2, R14.1, R15.1, RJ1.G-, RJ1.GND, RJ1.SHIELD0, RJ1.SHIELD1, RJ1.Y-, RTC.5 (NC1), RTC.6 (NC2), RTC.7 (NC3), RTC.8 (NC4), RTC.9 (NC5), RTC.10 (NC6), RTC.11 (NC7), RTC.12 (NC8), RTC.13 (GND), THM1.1 (GND)
IO8/A9: IC2.9 (CS)
IO9*/A10: CDR.1, R13.1
IO10*/A11: CON1.9
IO11*: CON1.7
IO13*: BKOUT.2, LCD.6
IRQ: NORDIC.8
LEDA: REA.2, RJ1.G+
LEDB: REB.2, RJ1.Y+
MISO: CON1.5, CON2.5, EMBD.2, IC2.6 (SO), ICSP.1, MICROSD.7 (DO), NORDIC.7, THM1.7 (DO)
MOSI: CON1.3, CON2.3, EMBD.3, IC2.7 (SI), ICSP.4, MICROSD.3 (DI), NORDIC.6
unnamed: CN1.D+, R2.1
unnamed: IC1.3 (D-), R3.2
unnamed: IC1.4 (D+), R2.2
unnamed: CN1.D-, R3.1
unnamed: B1.1, R7.1
unnamed: C8.2, IC1.17 (XTAL1), X1.P$2
unnamed: C9.2, IC1.16 (XTAL2), X1.P$1
unnamed: PWR1.A, R4.1
unnamed: R5.1, TXLED.C
unnamed: R6.2, RXLED.C
unnamed: EXT-SWITCH.2, F1.2, SW1.2
unnamed: C27.2, RN1.5 (2), RN1.6 (2)
unnamed: IC2.26 (LEDB), REB.1
unnamed: C26.1, IC2.1 (VCAP)
unnamed: IC2.14 (RBIAS), R15.2
unnamed: CX1.1, EXTL.P$2 (2), IC2.24 (OSC2)
unnamed: CX2.1, EXTL.P$1 (1), IC2.23 (OSC1)
unnamed: IC2.27 (LEDA), REA.1
unnamed: BATRTC.P$2 (+), RTC.14 (VBAT)
unnamed: FB1.1, THMC.2
unnamed: C20.1, FB1.2, THM1.2 (T-)
unnamed: FB2.1, THMC.1
unnamed: C20.2, FB2.2, THM1.3 (T+)
unnamed: CHG1.C, RC.1
unnamed: LIPO.5 (PROG), R1.2
unnamed: D1.A, EXT-CHG.2
RAW: EXT-SWITCH.1, LDO.1 (IN), LDO.3 (EN), SW1.1 (O)
RAW1: ISP-PWR.1
RD+: IC2.13 (TPIN+), RJ1.RD+, RN1.4 (1)
RD-: IC2.12 (TPIN-), RJ1.RD-, RN1.3 (1)
RST: BTN.B (S), BTN.B' (S1), IC1.13 (/RESET), IC2.10 (RESET), ICSP.5
RTC-32KHZ: BKOUT.4, RTC.1 (32KHZ)
RTC-INT: BKOUT.5, RTC.3 (!INT/SQW)
RTC-RST: BKOUT.6, RTC.4 (!RST)
RXLED/SS: RXLED.A
SCK: CON1.1, CON2.1, EMBD.1, IC2.8 (SCK), ICSP.3, MICROSD.5 (SCK), NORDIC.5, R12.2, THM1.5 (SCK)
SCK1: R14.2
SCL: BKOUT.7, BMP1.5 (SCL), OLEDADA.2, OLEDSD.4, R8.1, RTC.16 (SCL)
SDA: BKOUT.8, BMP1.6 (SDA), OLEDADA.1, OLEDSD.3, R9.1, RTC.15 (SDA)
TCT: C28.2, L1.1, RJ1.P4, RN1.7 (2), RN1.8 (2)
TD+: IC2.17 (TPOUT+), RJ1.TD+, RN1.2 (1)
TD-: IC2.16 (TPOUT-), RJ1.TD-, RN1.1
TXLED: TXLED.A
VBATT: C6.1, EXT-PWR1.2, EXT-PWR-F.2, F1.1, LIPO.3 (VBAT)
VBUS: CN1.VBUS, F2.1
VCC: C1.1, C14.1, C15.1, CHG1.A, D1.C, D2.C, L1.2, LIPO.4 (VIN)
VIN: CON1.10, CON2.10, EMBD.7

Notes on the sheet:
Ethernet
LED
RST
D/C
DIN
CLK
VCC
GND
LCD (Nokia 5110)
RTC
Breakout
Raspberry Pi / Beagle Bone
Humidity
Pressure
Thermocouple
THMC
Max Voltage Input: 16VDC
Max Current Output: 500mA
2K for 500mA charging
10K for 100mA charging
power circuit from Fio
Photocell
Bypassing
BUTTON
OLM-REV-5
OLED / SEEED
OLED / Adafruit
uSD
Radio
resistors can range from 2.2k to 10k

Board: 2 copper layers, 93 parts (0 on the bottom side), 60 nets, no tracks yet.

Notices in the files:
parts and their libraries:
microbuilder: This work is placed in the public domain, and may be freely used for commercial and non-commercial work with the following conditions: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
SparkFun-Connectors: Licensing: CC v3.0 Share-Alike You are welcome to use this library for commercial purposes.
